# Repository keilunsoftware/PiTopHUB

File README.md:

# PiTopHUB
PiTop addon board with Arduino ATMEGA328P programming and breakout

Features:

- USB Hub with 2 free ports and WDPi usb (WDPi can be installed on top of PiTop power hub)
- Full Arduino compatible breakout board (programmable from RPi)
- PiTop 16-18V power connector
- Full RPi GPIO connector (removed permanent 3v3 pin to avoid battery drain, even when off)
- Pin connector for TinyRTC module (battery on top)

Known issues:

- With permanent USB devices connected to RPi USB PiTop experiences a battery drain even when powered off. Need to add an additional switch on the RPi USB power cable

Order PCB directly from OSH Park: https://oshpark.com/shared_projects/OJJPJsZg

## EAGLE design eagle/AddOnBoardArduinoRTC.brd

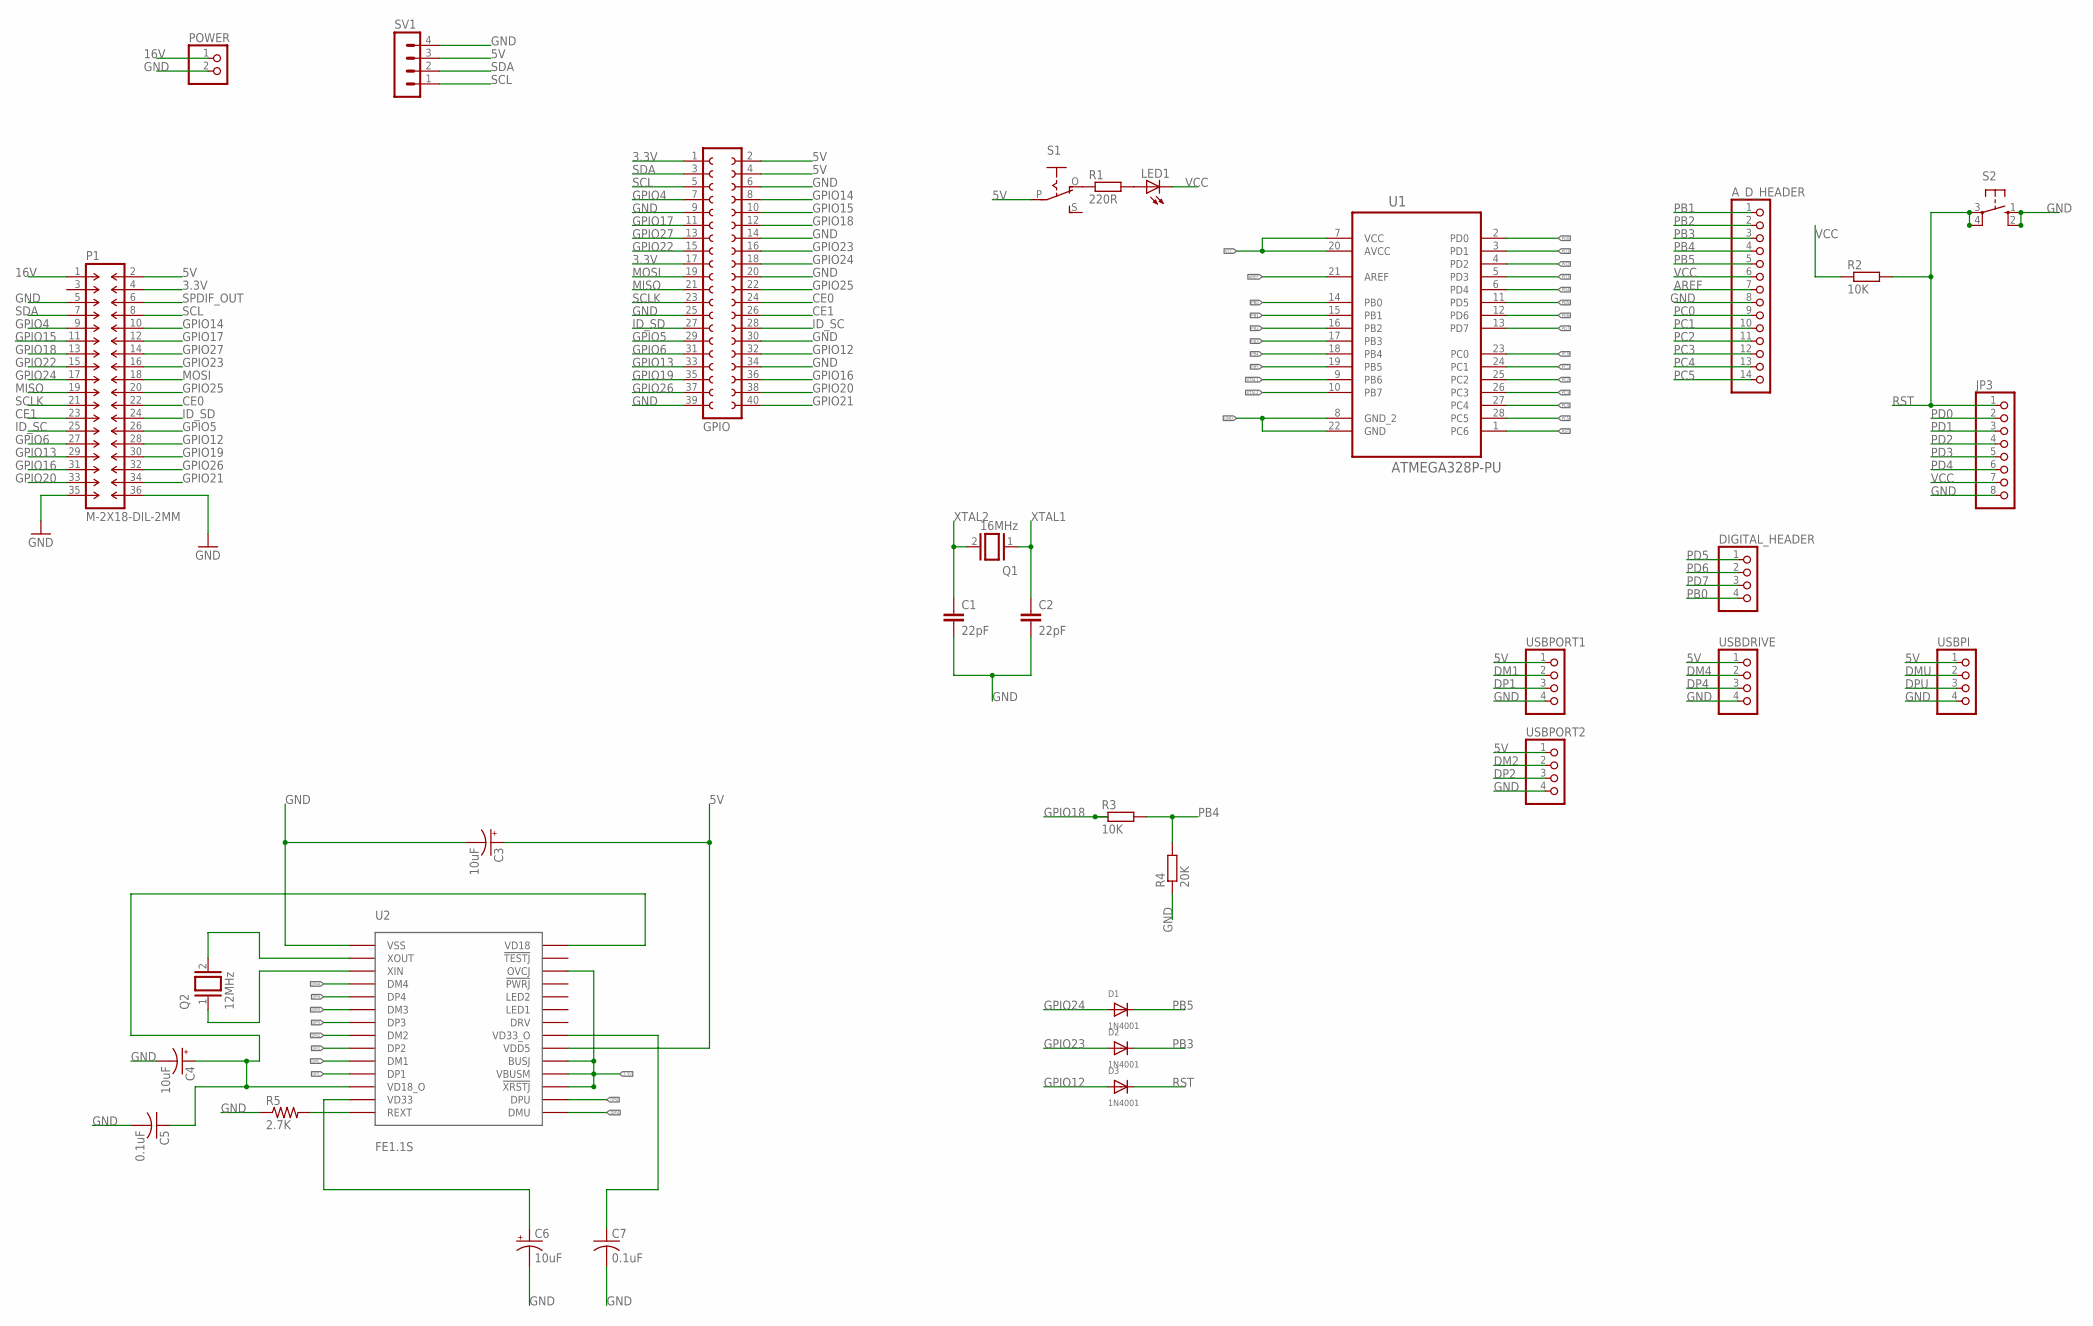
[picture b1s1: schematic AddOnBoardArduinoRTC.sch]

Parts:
A_D_HEADER: PINHD-1X14; 1X14
C1, C2: 22pF; C025-024X044
C3, C4, C6: 10uF; 153CLV-0605
C5, C7: 0.1uF; C1206
D1, D2, D3: 1N4001; SMADIODE
DIGITAL_HEADER: PINHD-1X4; 1X04
GPIO: FE20-2
JP3: PINHD-1X8; 1X08
LED1: LED5MM
P1: M-2X18-DIL-2MM; DIL-2MM-2X18
POWER: PINHD-1X2; 1X02
Q1: 16MHz; QS
Q2: 12MHz; QS
R1: 220R; M1206
R2, R3: 10K; M1206
R4: 20K; M1206
R5: 2.7K; M1206
S1: EG1218S; EG1218
S2: 10-XX; B3F-10XX
SV1: MA04-1
U1: ATMEGA328P-PU; DIP254P762X457-28
U2: FE1.1S; SSOP-28
USBDRIVE: PINHD-1X4; 1X04
USBPI: PINHD-1X4; 1X04
USBPORT1, USBPORT2: PINHD-1X4; 1X04

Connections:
3.3V: GPIO.1, GPIO.17, P1.4, U2.17 (!XRSTJ), U2.18 (VBUSM), U2.19 (BUSJ), U2.26 (OVCJ)
5V: C3.+, GPIO.2, GPIO.4, P1.2, S1.P, SV1.3, U2.20 (VDD5), USBDRIVE.1, USBPI.1, USBPORT1.1, USBPORT2.1
16V: P1.1, POWER.1
AREF: A_D_HEADER.7, U1.21 (AREF)
CE0: GPIO.24, P1.22
CE1: GPIO.26, P1.23
DM1: U2.10 (DM1), USBPORT1.2
DM2: U2.8 (DM2), USBPORT2.2
DM3: U2.6 (DM3)
DM4: U2.4 (DM4), USBDRIVE.2
DMU: U2.15 (DMU), USBPI.2
DP1: U2.11 (DP1), USBPORT1.3
DP2: U2.9 (DP2), USBPORT2.3
DP3: U2.7 (DP3)
DP4: U2.5 (DP4), USBDRIVE.3
DPU: U2.16 (DPU), USBPI.3
GND: A_D_HEADER.8, C1.2, C2.2, C3.-, C4.-, C5.2, C6.-, C7.2, GPIO.6, GPIO.9, GPIO.14, GPIO.20, GPIO.25, GPIO.30, GPIO.34, GPIO.39, JP3.8, P1.5, P1.35, P1.36, POWER.2, R4.1, R5.1, S2.1 (S), S2.2 (S1), SV1.4, U1.8 (GND_2), U1.22 (GND), U2.1 (VSS), USBDRIVE.4, USBPI.4, USBPORT1.4, USBPORT2.4
GPIO4: GPIO.7, P1.9
GPIO5: GPIO.29, P1.26
GPIO6: GPIO.31, P1.27
GPIO12: D3.A, GPIO.32, P1.28
GPIO13: GPIO.33, P1.29
GPIO14: GPIO.8, P1.10
GPIO15: GPIO.10, P1.11
GPIO16: GPIO.36, P1.31
GPIO17: GPIO.11, P1.12
GPIO18: GPIO.12, P1.13, R3.1
GPIO19: GPIO.35, P1.30
GPIO20: GPIO.38, P1.33
GPIO21: GPIO.40, P1.34
GPIO22: GPIO.15, P1.15
GPIO23: D2.A, GPIO.16, P1.16
GPIO24: D1.A, GPIO.18, P1.17
GPIO25: GPIO.22, P1.20
GPIO26: GPIO.37, P1.32
GPIO27: GPIO.13, P1.14
ID_SC: GPIO.28, P1.25
ID_SD: GPIO.27, P1.24
MISO: GPIO.21, P1.19
MOSI: GPIO.19, P1.18
unnamed: Q2.2, U2.2 (XOUT)
unnamed: Q2.1, U2.3 (XIN)
unnamed: R5.2, U2.14 (REXT)
unnamed: C6.+, U2.13 (VD33)
unnamed: C4.+, C5.1, U2.12 (VD18_O), U2.28 (VD18)
unnamed: C7.1, U2.21 (VD33_O)
unnamed: R1.1, S1.O
unnamed: LED1.A, R1.2
PB0: DIGITAL_HEADER.4, U1.14 (PB0)
PB1: A_D_HEADER.1, U1.15 (PB1)
PB2: A_D_HEADER.2, U1.16 (PB2)
PB3: A_D_HEADER.3, D2.C, U1.17 (PB3)
PB4: A_D_HEADER.4, R3.2, R4.2, U1.18 (PB4)
PB5: A_D_HEADER.5, D1.C, U1.19 (PB5)
PC0: A_D_HEADER.9, U1.23 (PC0)
PC1: A_D_HEADER.10, U1.24 (PC1)
PC2: A_D_HEADER.11, U1.25 (PC2)
PC3: A_D_HEADER.12, U1.26 (PC3)
PC4: A_D_HEADER.13, U1.27 (PC4)
PC5: A_D_HEADER.14, U1.28 (PC5)
PD0: JP3.2, U1.2 (PD0)
PD1: JP3.3, U1.3 (PD1)
PD2: JP3.4, U1.4 (PD2)
PD3: JP3.5, U1.5 (PD3)
PD4: JP3.6, U1.6 (PD4)
PD5: DIGITAL_HEADER.1, U1.11 (PD5)
PD6: DIGITAL_HEADER.2, U1.12 (PD6)
PD7: DIGITAL_HEADER.3, U1.13 (PD7)
RST: D3.C, JP3.1, R2.2, S2.3, S2.4 (P1), U1.1 (PC6)
SCL: GPIO.5, P1.8, SV1.1
SCLK: GPIO.23, P1.21
SDA: GPIO.3, P1.7, SV1.2
SPDIF_OUT: P1.6
VCC: A_D_HEADER.6, JP3.7, LED1.K (C), R2.1, U1.7 (VCC), U1.20 (AVCC)
XTAL1: C2.1, Q1.1, U1.9 (PB6)
XTAL2: C1.1, Q1.2, U1.10 (PB7)

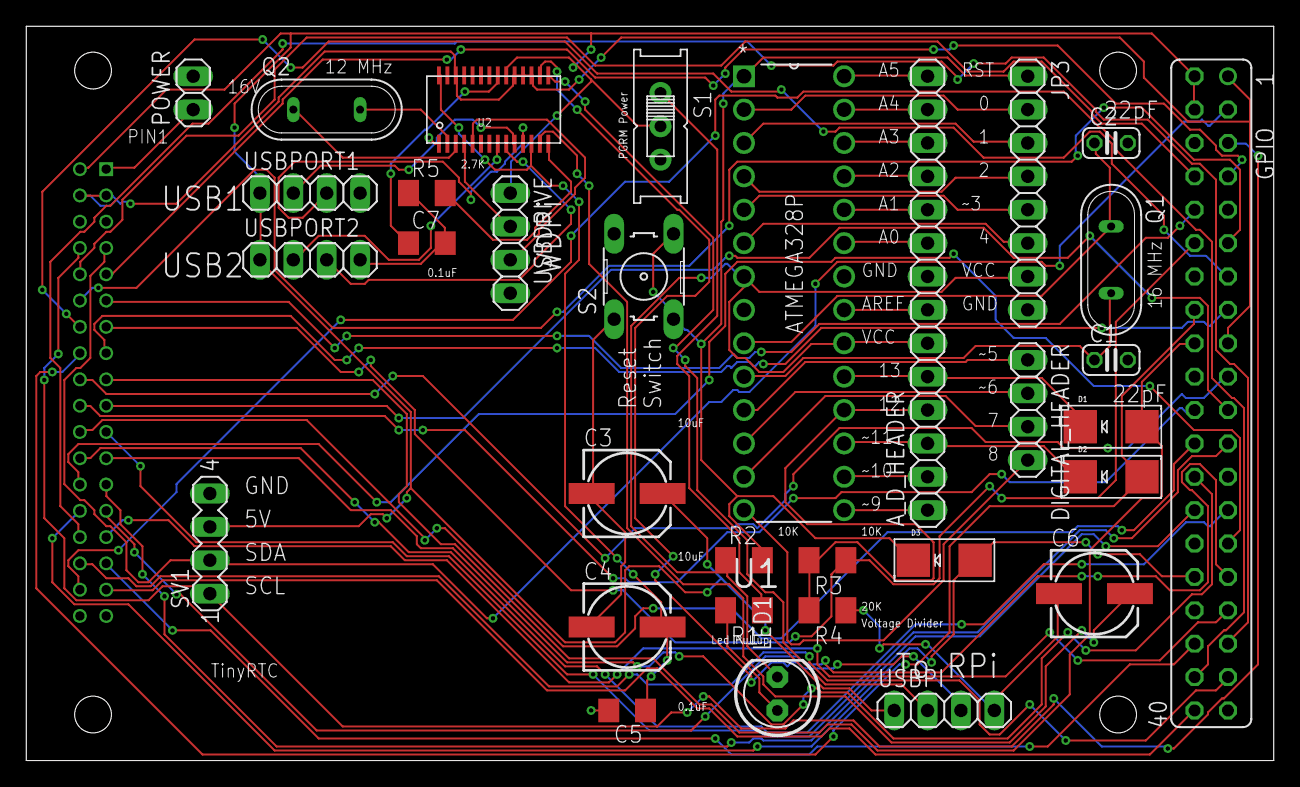
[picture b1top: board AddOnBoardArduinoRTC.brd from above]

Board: 2 copper layers, 94.9 x 55.9 mm, 33 parts (1 on the bottom side), 73 nets.

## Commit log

2016-11-02 Added Eagle Schematics and Board layout
2016-11-02 Added further description, features, known issues
2016-11-02 Added TinyRTC feature
2016-11-02 Added OSH Park Direct PCB order link

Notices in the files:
parts and their libraries:
con-headers-jp: Copyright (C) 2008, Bob Starr
